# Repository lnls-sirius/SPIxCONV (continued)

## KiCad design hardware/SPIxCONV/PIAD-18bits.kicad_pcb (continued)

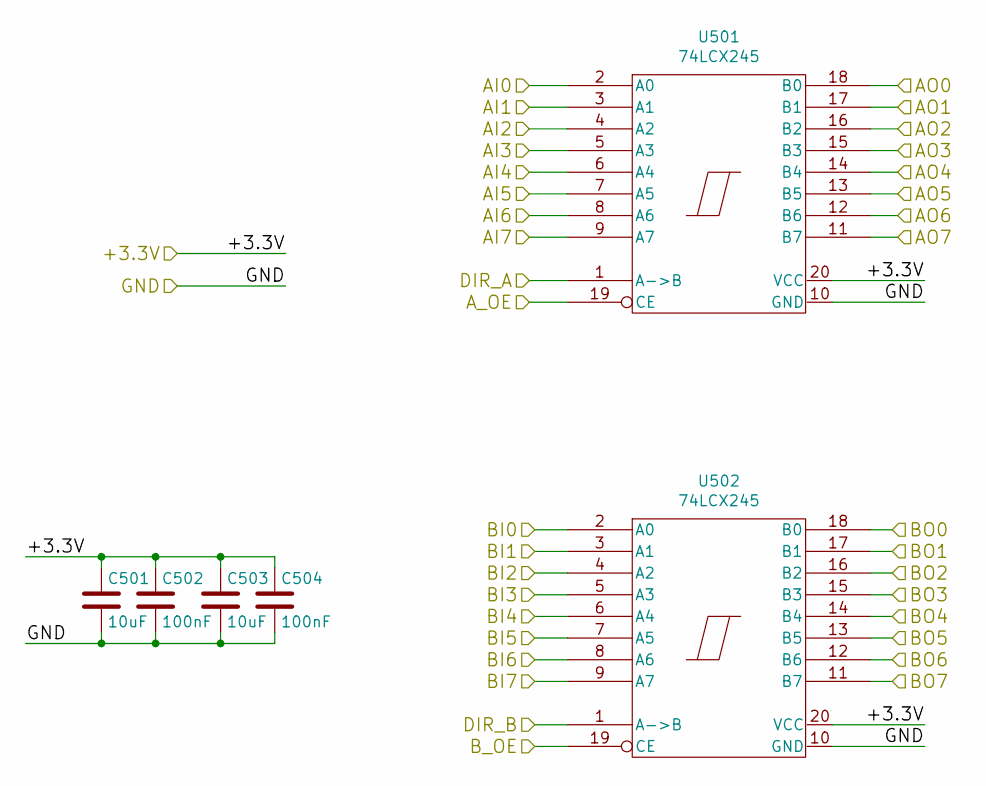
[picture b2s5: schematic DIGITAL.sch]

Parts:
C501, C503: 10uF; C_0805
C502, C504: 100nF; C_0805
U501, U502: 74LCX245; SOIC-20W_7.5x12.8mm_Pitch1.27mm

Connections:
+3V3: C501.1, C502.1, C503.1, C504.1, U501.20 (VCC), U502.20 (VCC); also elsewhere on the board
/DA0: U501.2 (A0); also elsewhere on the board
/DA1: U501.3 (A1); also elsewhere on the board
/DA2: U501.4 (A2); also elsewhere on the board
/DA3: U501.5 (A3); also elsewhere on the board
/DA4: U501.6 (A4); also elsewhere on the board
/DA5: U501.7 (A5); also elsewhere on the board
/DA6: U501.8 (A6); also elsewhere on the board
/DA7: U501.9 (A7); also elsewhere on the board
/DB0: U502.2 (A0); also elsewhere on the board
/DB1: U502.3 (A1); also elsewhere on the board
/DB2: U502.4 (A2); also elsewhere on the board
/DB3: U502.5 (A3); also elsewhere on the board
/DB4: U502.6 (A4); also elsewhere on the board
/DB5: U502.7 (A5); also elsewhere on the board
/DB6: U502.8 (A6); also elsewhere on the board
/DB7: U502.9 (A7); also elsewhere on the board
/DIR_A: U501.1 (A->B); also elsewhere on the board
/DIR_B: U502.1 (A->B); also elsewhere on the board
/PA0: U501.18 (B0); also elsewhere on the board
/PA1: U501.17 (B1); also elsewhere on the board
/PA2: U501.16 (B2); also elsewhere on the board
/PA3: U501.15 (B3); also elsewhere on the board
/PA4: U501.14 (B4); also elsewhere on the board
/PA5: U501.13 (B5); also elsewhere on the board
/PA6: U501.12 (B6); also elsewhere on the board
/PA7: U501.11 (B7); also elsewhere on the board
/PB0: U502.18 (B0); also elsewhere on the board
/PB1: U502.17 (B1); also elsewhere on the board
/PB2: U502.16 (B2); also elsewhere on the board
/PB3: U502.15 (B3); also elsewhere on the board
/PB4: U502.14 (B4); also elsewhere on the board
/PB5: U502.13 (B5); also elsewhere on the board
/PB6: U502.12 (B6); also elsewhere on the board
/PB7: U502.11 (B7); also elsewhere on the board
GND: C501.2, C502.2, C503.2, C504.2, U501.10 (GND), U501.19 (CE), U502.10 (GND), U502.19 (CE); also elsewhere on the board

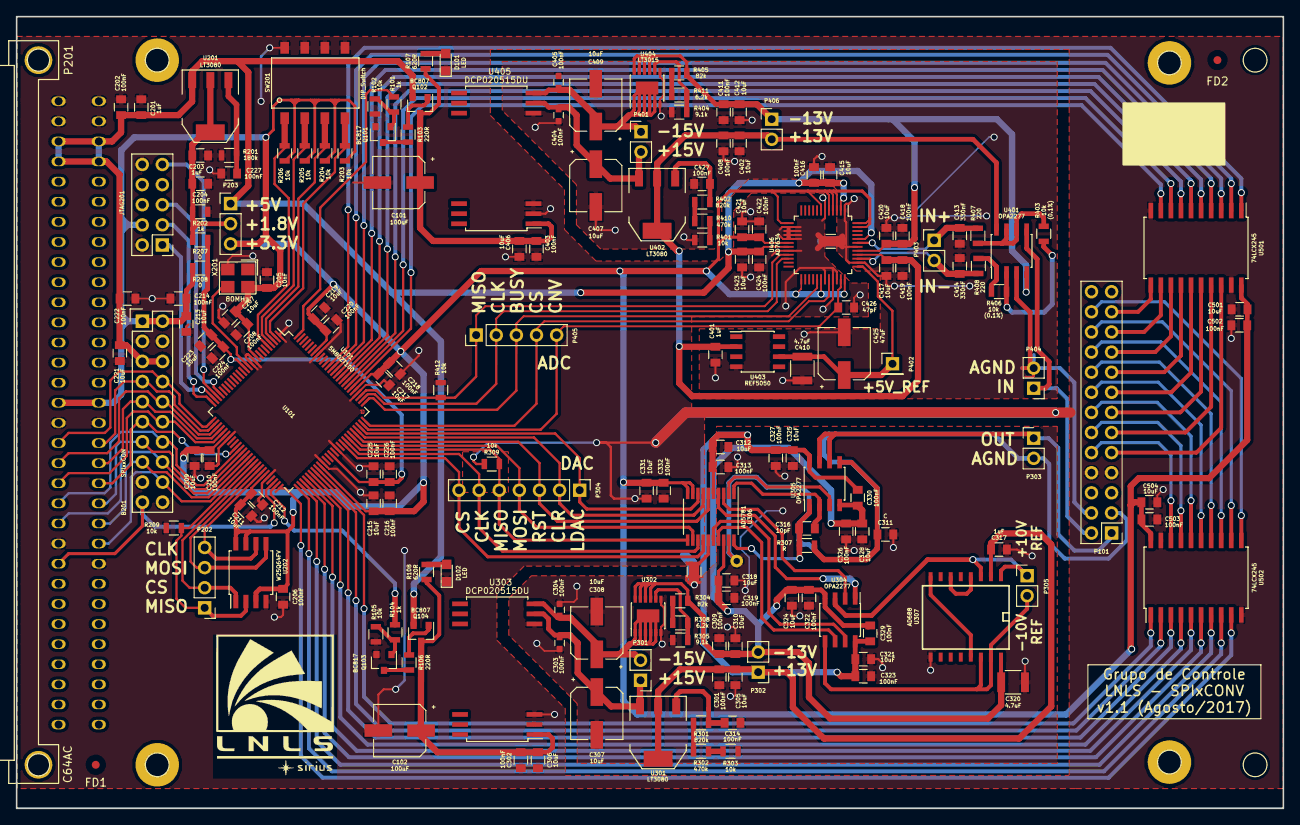
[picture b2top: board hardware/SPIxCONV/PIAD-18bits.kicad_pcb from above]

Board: 2 copper layers, 160.0 x 100.0 mm, 178 parts (0 on the bottom side), 130 nets.

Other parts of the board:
FD1, FD4: Fiducial_1mm_Dia_2.54mm_Outer_CopperBottom
FD2, FD3: Fiducial_1mm_Dia_2.54mm_Outer_CopperTop

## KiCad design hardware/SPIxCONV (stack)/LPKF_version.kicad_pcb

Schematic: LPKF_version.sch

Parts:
Beagle101: BeagleBone; BEAGLEBONEBLACK
P101: CONN_01X05; Pin_Header_Straight_1x05_Pitch2.54mm
P102: CONN_01X07; Pin_Header_Straight_1x07_Pitch2.54mm
P103: CONN_02X02; Pin_Header_Straight_2x02_Pitch2.54mm
P104, P105, P106, P107: CONN_01X01; ground_plane_via
P108: CONN_01X02; Pin_Header_Straight_1x02_Pitch2.54mm
P109: CONN_01X01; Pin_Header_Straight_1x01_Pitch2.54mm
U101, U102: HC245; SOIC-20W_7.5x12.8mm_Pitch1.27mm

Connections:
/+5V: Beagle101.C5, Beagle101.C6, P108.1, P108.2, U101.20, U102.20
/ADC_BUSY: P101.3, U102.7
/ADC_CLK: P101.2, U102.8
/ADC_CNV: P101.5, U102.5
/ADC_CS: P101.4, U102.6
/ADC_MISO: P101.1, U102.9
/DAC_CLK: P102.6, U101.3
/DAC_CLR: P102.2, U101.7
/DAC_CS: P102.7, U101.2
/DAC_LDAC: P102.1, U101.8
/DAC_MISO: P102.5, U101.4
/DAC_MOSI: P102.4, U101.5
/DAC_RST: P102.3, U101.6
/GPIO_BUSY: Beagle101.C16, U102.13
/GPIO_CLR: Beagle101.C25, U101.13
/GPIO_CNV: Beagle101.C14, U102.15
/GPIO_LDAC: Beagle101.C24, U101.12
/GPIO_RST: Beagle101.C26, U101.14
/PWR_SYS: Beagle101.C23, P109.1
/SPI0_CS: Beagle101.C17, U102.14
/SPI0_MISO: Beagle101.C18, U102.11
/SPI0_SCLK: Beagle101.C22, U102.12
/SPI1_CS0: Beagle101.C28, U101.18
/SPI1_MISO: Beagle101.C30, U101.16
/SPI1_MOSI: Beagle101.C29, U101.15
/SPI1_SCLK: Beagle101.C31, U101.17
GND: Beagle101.C1, Beagle101.C2, Beagle101.C43, Beagle101.C44, Beagle101.C45, Beagle101.C46, P103.1, P103.2, P103.3, P103.4, U101.1, U101.10, U101.19, U102.1, U102.10, U102.19

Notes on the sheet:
SPI0: ADC SPI1: DAC

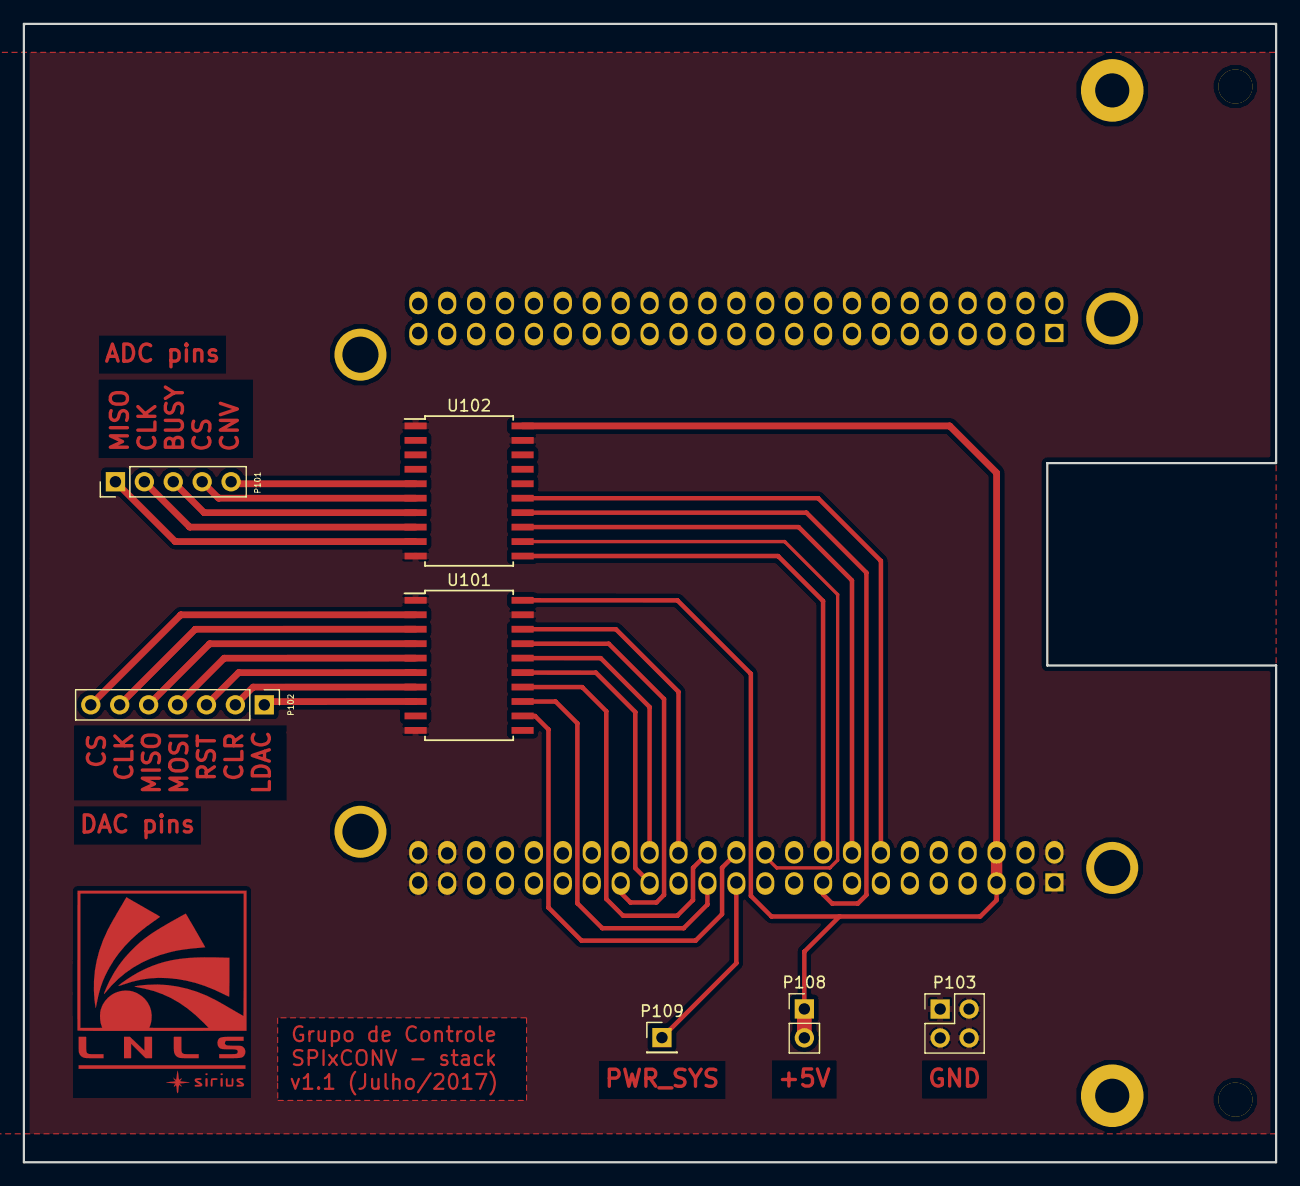
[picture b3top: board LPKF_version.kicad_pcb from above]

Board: 2 copper layers, 110.0 x 100.0 mm, 13 parts (1 on the bottom side), 27 nets.

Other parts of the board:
P102#2: CONN_01X07; LNLS_LOGO_Silk

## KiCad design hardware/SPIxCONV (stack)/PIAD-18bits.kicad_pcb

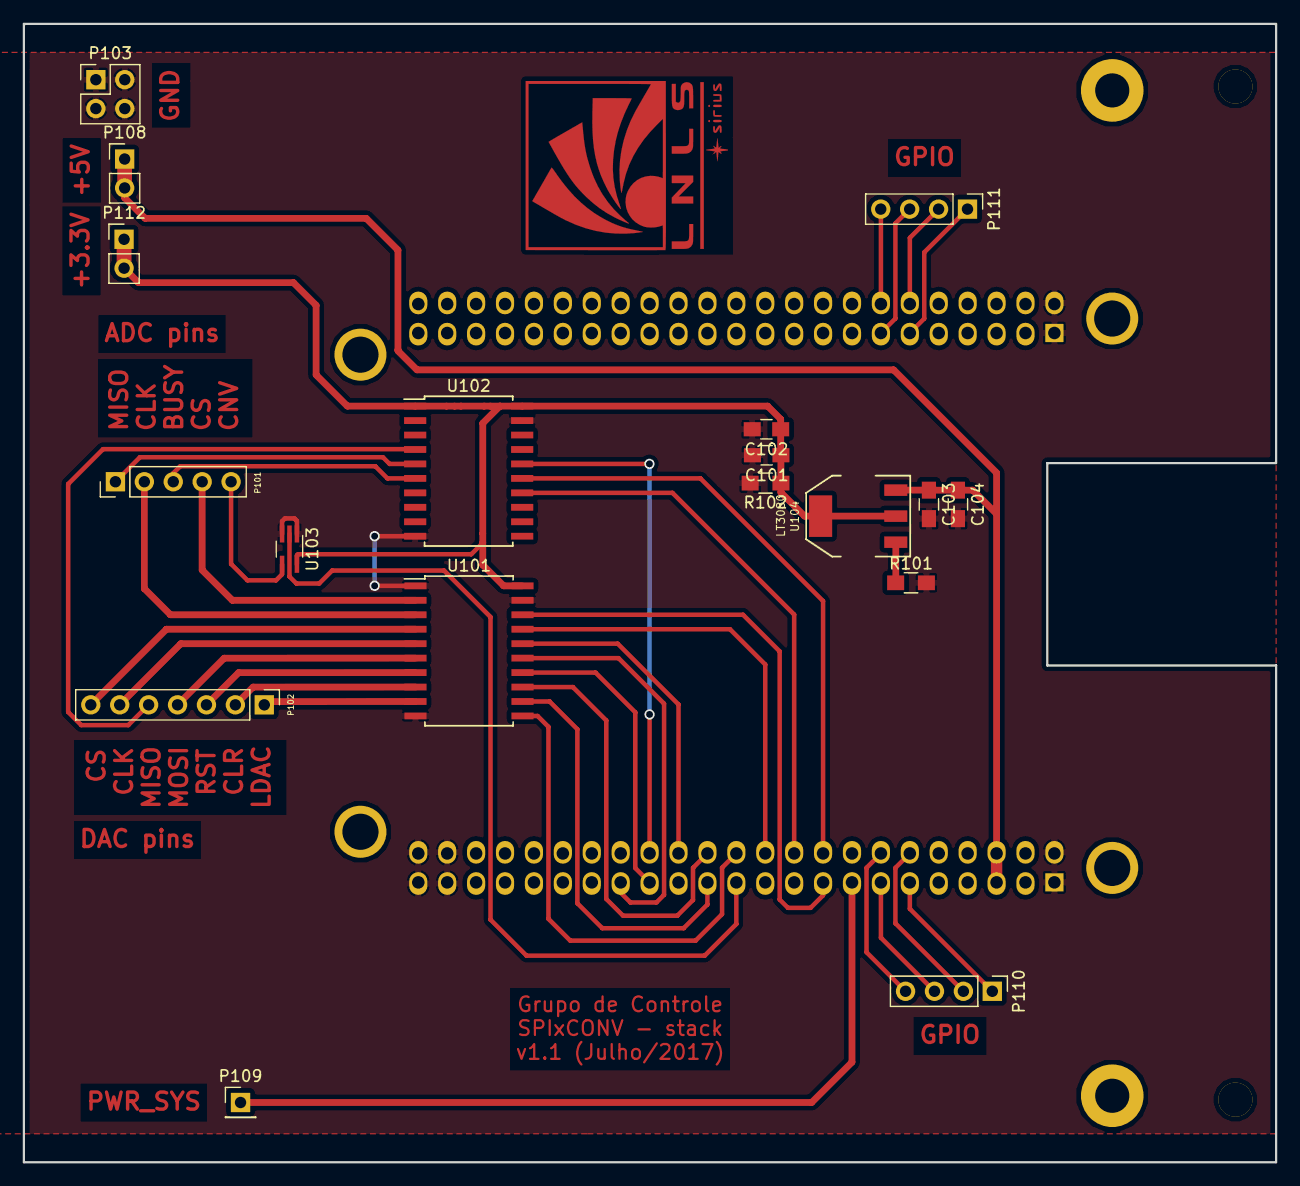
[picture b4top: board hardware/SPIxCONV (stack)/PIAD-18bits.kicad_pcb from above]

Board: 2 copper layers, 110.0 x 100.0 mm, 24 parts (1 on the bottom side), 36 nets.

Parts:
Beagle101: BeagleBone; BEAGLEBONEBLACK
C101, C103: 1uF; C_0805_HandSoldering
C102, C104: 100nF; C_0805_HandSoldering
P101: CONN_01X05; Pin_Header_Straight_1x05_Pitch2.54mm
P102: CONN_01X07; Pin_Header_Straight_1x07_Pitch2.54mm
P102#2: CONN_01X07; LNLS_LOGO_Silk
P103: CONN_02X02; Pin_Header_Straight_2x02_Pitch2.54mm
P104, P105, P106, P107: CONN_01X01; ground_plane_via
P108, P112: CONN_01X02; Pin_Header_Straight_1x02_Pitch2.54mm
P109: CONN_01X01; Pin_Header_Straight_1x01_Pitch2.54mm
P110, P111: CONN_01X04; Pin_Header_Straight_1x04_Pitch2.54mm
R101: 330k; R_0805_HandSoldering
R102: 1k; R_0805_HandSoldering
U101, U102: 74LCX245; SOIC-20W_7.5x12.8mm_Pitch1.27mm
U103: 74LS125; SOT-353_SC-70-5_Handsoldering
U104: LT3080; SOT-223

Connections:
/+3.3V: C101.1, C102.1, P112.1, P112.2, R102.1, U101.20, U102.1, U102.20, U104.2, U104.4
/+5V: Beagle101.C5, Beagle101.C6, C103.1, C104.1, P108.1, P108.2, U104.3
/ADC_BUSY: P101.3, U102.6
/ADC_CLK: P101.2, U101.3
/ADC_CS: P101.4, U101.2
/ADC_MISO: P101.1, U102.5
/DAC_CLK: P102.6, U101.5
/DAC_CLR: P102.2, U101.8
/DAC_CS: P102.7, U101.4
/DAC_LDAC: P102.1, U101.9
/DAC_MISO: P102.5, U102.4
/DAC_MOSI: P102.4, U101.6
/DAC_RST: P102.3, U101.7
/GPIO_0: Beagle101.C11, P110.1
/GPIO_1: Beagle101.C12, P110.2
/GPIO_2: Beagle101.C13, P110.3
/GPIO_3: Beagle101.C14, P110.4
/GPIO_4: Beagle101.B11, P111.1
/GPIO_5: Beagle101.B12, P111.2
/GPIO_6: Beagle101.B13, P111.3
/GPIO_7: Beagle101.B14, P111.4
/GPIO_BUSY: Beagle101.C20, U102.14
/GPIO_CLR: Beagle101.C25, U101.12
/GPIO_CNV: Beagle101.C23, U103.2
/GPIO_LDAC: Beagle101.C24, U101.11
/GPIO_RST: Beagle101.C26, U101.13
/PWR_SYS: Beagle101.C15, P109.1
/SPI0_CS: Beagle101.C17, U101.18
/SPI0_MISO: Beagle101.C18, U102.15
/SPI0_SCLK: Beagle101.C22, U101.17
/SPI1_CS0: Beagle101.C28, U101.16
/SPI1_MISO: Beagle101.C30, U102.16
/SPI1_MOSI: Beagle101.C29, U101.14
/SPI1_SCLK: Beagle101.C31, U101.15
GND: Beagle101.B1, Beagle101.B2, Beagle101.C1, Beagle101.C2, Beagle101.C43, Beagle101.C44, Beagle101.C45, Beagle101.C46, C101.2, C102.2, C103.2, C104.2, P103.1, P103.2, P103.3, P103.4, R101.2, R102.2, U101.1, U101.10, U101.19, U102.10, U102.19, U103.1, U103.3
unnamed: R101.1, U104.1

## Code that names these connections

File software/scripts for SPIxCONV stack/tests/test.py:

#!/usr/bin/python3

from Adafruit_BBIO.SPI import SPI
import Adafruit_BBIO.GPIO as GPIO
import time
#-------------------------------------------------------
# initialize the bus and device /dev/spidev1.0
spi0 = SPI(0,0)     #ADC
# initialize the bus and device /dev/spidev2.0
spi1 = SPI(1,0)     #DAC
#-------------------------------------------------------
#Set the maximum clock frequency
spi0.msh=100000
spi1.msh=100000
#-------------------------------------------------------
# mnemonics for GPIO
RST = "P9_26"
CLR = "P9_25"
LDAC = "P9_24"
BUSY = "P9_20"
CNV = "P9_23"
PWR_SYS = "P9_16"
#PWR_SYS = "P9_15"
#-------------------------------------------------------
# defining outputs
GPIO.setup(RST, GPIO.OUT)
GPIO.setup(CLR, GPIO.OUT)
GPIO.setup(LDAC, GPIO.OUT)
GPIO.setup(CNV, GPIO.OUT)
GPIO.setup(PWR_SYS, GPIO.OUT)
#-------------------------------------------------------
# defining inputs
GPIO.setup(BUSY, GPIO.IN)
#-------------------------------------------------------
# initialization of outputs
GPIO.output(RST, GPIO.LOW)
GPIO.output(CLR, GPIO.LOW)
GPIO.output(LDAC, GPIO.LOW)
GPIO.output(CNV, GPIO.LOW)
GPIO.output(PWR_SYS, GPIO.LOW)
#=======================================================
#	pinout for DAC and ADC bus
#=======================================================
'''
DAC pins
	SPI1_CS:	"P9_28"
	SPI1_SCLK:	"P9_31"
	SPI1_MOSI:	"P9_29"
	SPI1_MISO:	"P9_30"
	GPIO_RST:	"P9_26"
	GPIO_CLR:	"P9_25"
	GPIO_LDAC:	"P9_24"

ADC pins
	SPI0_CS:	"P9_17"
	SPI0_SCLK:	"P9_22"
	SPI0_MISO:	"P9_18"
	GPIO_BUSY:	"P9_20"
	GPIO_CNV:	"P9_23"

GPIO pins
	GPIO_0: "P9_11"
	GPIO_1: "P9_12"
	GPIO_2: "P9_13"
	GPIO_3: "P9_14"

	GPIO_4: "P8_11"
	GPIO_5: "P8_12"
	GPIO_6: "P8_13"
	GPIO_7: "P8_14"

POWER SYSTEM:
	PWR_SYS = "P9_16"
'''
#=======================================================
#	testing SPI
#=======================================================

while(1):
	# RST = 1 --> address
#	GPIO.output(RST, GPIO.HIGH)
#	time.sleep(0.001)
	# RST = 0 --> slaves
#	GPIO.output(RST, GPIO.LOW)
#	time.sleep(0.001)

	# send data through SPI
	spi1.writebytes([0x20, 0x03, 0x12])
	spi0.writebytes([0x02, 0x30, 0x21])

#	GPIO.output(PWR_SYS, GPIO.HIGH)
#	GPIO.output(RST, GPIO.HIGH)
#	GPIO.output(CLR, GPIO.HIGH)
#	GPIO.output(LDAC, GPIO.HIGH)
#	GPIO.output(CNV, GPIO.HIGH)

#	GPIO.output(PWR_SYS, GPIO.LOW)
#	GPIO.output(RST, GPIO.LOW)
#	GPIO.output(CLR, GPIO.LOW)
#	GPIO.output(LDAC, GPIO.LOW)
#	GPIO.output(CNV, GPIO.LOW)

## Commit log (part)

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2016-11-03 Added protection by new line on ConfigByHotname file
2018-12-07 SPIxCONV project cloned from LNLS internal git server
2018-12-07 added "cpld" folder with email for contact
2019-01-14 splitted default window (EPP_SPIxCONV) in Kicker and Septum
2019-01-31 Added support for TCP.
2019-01-31 Removed with resource in order to use Python 2
2019-01-31 Incorrect ident.
2019-01-31 Added logging information to function on(addr)
2019-01-31 Removed comments and fixed bugs when logging server_address
2019-01-31 Fixed a bug in the selection script by adding and %8 operation on the checks.
2019-02-11 Removed logger from DAC.
2019-02-11 Added argparse.ArgumentDefaultsHelpFormatter.
2019-02-19 minor changes
2019-02-19 added "return" value to functions in flash.py
2019-02-28 updated PV name from "PREFIX:PwrState-Mon" to "PREFIX:PwrState-Sts" in CSS displays
2019-03-06 changed executable permission of config-pin
2019-03-06 pinout documentation review
2019-03-06 first PyDM display added
2019-03-06 PyDM ui displays added
2019-05-03 minor changes in displays
2019-05-03 system variables edited in SPIxCONV protocol file
2019-05-07 remaining Pulsed Magnets displays added
2019-05-08 graphs for Voltage-Mon deleted
2019-05-14 ADC measure returning maximum of 10 last samples
2019-05-27 pydm: Added a desktop icon and an install script
2019-06-03 desktop shortcut added
2019-07-27 fixed displays function names
2019-10-07 added multiple devices displays
2019-10-25 changed bit 4 of port B to output (port B: 3 inputs, 5 outputs)
2020-01-06 Support for python3
    Python2 will be deprecated. Changes on "print" commands!
2020-01-28 removed board address ID dependency (requirement: one BBB for each SPIxCONV)
2020-02-04 fixed board address detection bug
2020-02-04 uncommented board_address argument
2020-02-04 discarded board ID (data[0]) information sent by IOC
2020-02-04 bug fixed
2020-02-04 discarded args.board_address information from config
2020-05-15 docs dir added
2020-05-15 [docs] added Sphinx source & build dir
2020-05-15 Â[docs] added github target in Makefile
2020-05-15 [docs] added gh-pages files
2020-05-15 [docs] Makefile updated
2020-05-22 [docs] gh-pages branch initialized
2020-07-13 [voltage-adjustment] queue architecture adopted
2020-07-13 [voltage-adjustment] voltage adjustment commands queue added
2020-07-13 [pulse-sts] pin direction configured
2020-07-13 [voltage-adjustment] fields added to DAC output message (voltage factor, step trigger and delay)
2020-07-14 [voltage-adjustment] fixed fields in DAC output message
2020-07-15 [voltage-adjustment] voltage steps implemented
2020-07-15 [voltage-RB] voltage RB measure at IOC initialization
2020-07-15 [voltage-adjustment] started fix for power PS on with setpoint
2020-07-16 [voltage-adjustment] finished fix for power PS on with setpoint
2020-07-16 [voltage-adjustment] removed print line
2020-07-16 [voltage-adjustment] check last voltage setpoint at code initialization
2020-07-16 [voltage-adjustment] use PwrState-Sel instead of PwrState-Sts for algorithm
2020-07-17 Commented unnecessary protocol code
2020-07-22 [voltage-steps] included hostname support to initialize steps vars
2020-07-22 [voltage-steps] removed rule to adjust setpoint directly if PS is off
2020-07-22 [voltage-steps] last_setpoint fix
2020-07-22 [voltage-steps] last_setpoint initialization
2020-07-22 [voltage-steps] included debug logs for voltage adjustment
2020-07-22 [voltage-steps] changed log level from debug to info
2020-07-22 [voltage-steps] logs added
2020-07-22 [voltage-steps] logs related to hostname added
2020-07-22 [voltage-steps] ensure RB is equal to RB
2020-07-22 [voltage-steps] send SP to RB
2020-07-27 [voltage-steps] added try/except for threads 2 and 3
2020-07-27 [voltage-steps] changed identifier from hostname to ip address
2020-07-27 [voltage-steps] included steps var in identifier
2020-07-27 [voltage-steps] started using terminator for messages (CR+LF)
2020-07-29 [voltage-adjustment] removed print and added terminator characters (CR+LF)
2020-07-29 [voltage-adjustment] lock support to avoid race conditions included
2020-07-30 [voltage-adjustment] changed logs setpoint unit (from code to voltage)
2020-07-30 [voltage-adjustment] included step number in logs (for gradual adjustments)
2020-07-30 [voltage-adjustment] restored rule to stop gradual adjustments if a new setpoint is received
2020-07-30 [voltage-adjustment] PS on/off & Pulse on/off logs included
2020-07-30 [voltage-adjustment] added logs to write commands
2020-07-31 [voltage-adjustment] changed line split method (break only CR+LF)
2020-07-31 [voltage-adjustment] changed command 0x0D to 0x11
2020-08-14 hostname support for spares
2020-08-17 general spare support added
2020-09-15 [readme] simple description added
2020-09-15 hardware figures dir created
2020-09-15 [readme] cut figures and added them to readme
2020-09-15 [readme] pcb figs and link to github-page added
2020-09-16 connectors figure added
2020-09-16 [readme] connectors image added
2020-09-16 [readme] GPIO expander board info added
2020-09-16 [readme] main board and gpio stack added
2020-09-17 [readme] main board image added
2020-09-17 [readme] software files location added
2020-09-17 [readme] code, known problems, faq sections added under software section
2020-09-17 [readme] software description added
2020-09-17 [readme] OPI section added
2020-09-17 Update README.md: Fix broken image link
2020-09-17 [readme] OPI image added
2020-09-17 [readme] updated images
2020-09-17 [readme] side-by-side images
2020-09-17 [readme] fixed broken links
2020-09-17 [readme] images config updated
2020-09-17 [readme] images updated
2020-09-17 [readme] CPLD pinout added
2020-09-18 figure rotated (main board)
2020-09-18 gpio images rotated
2020-09-18 main board figures rotated
2020-09-18 figures path updated
2020-09-21 [readme] figures updated
2020-09-21 [readme] main board division figures added
2020-09-21 [readme] main board: testpoints figures added
2020-09-21 [readme] gpio stack: testpoints figures added
2020-09-21 [readme] main board division updated
2020-09-23 [documentation] fixed dac & adc selections
2020-09-23 [documentation] fixed typo in CPLD connector figure
2020-09-23 [documentation] figures of interface connectors in GPIO stack updated
2020-09-23 [readme] add calibration figures
2020-09-23 [readme] add CPLD figures
2020-09-23 [readme] main board testpoint section created
2020-09-23 [readme] gpio test point section created
2020-09-23 [documentation] changed figures extension (png --> jpg)
2020-09-23 [documentation] images compressed (jpeg)
2020-09-23 [readme] images extension updated (jpeg)
2020-09-23 [documentation] figures updated (rotated, cut, divison redone)
2020-09-23 [readme] voltmeter datasheet added and calibration section updated
2020-09-23 [readme] add calibration data
2020-09-23 [readme] fixed calibration data table
2020-09-23 [readme] add known problems
2020-11-12 correction from last commit
2020-11-12 loop while-pass removed
2021-02-23 Adding config with hostname info
2021-03-19 Added analog feedback project
2021-05-05 Added configuration to set the BBB hostname via an external flash drive
2021-05-06 Removed pycache
2021-05-06 Added umont /dev/sda command
2021-09-30 Redis script for Voltage Feedback
2021-09-30 Script update
2023-02-06 upgrading code for new nlk
2023-02-06 removing unused files
2023-02-06 config at ioc startup
2023-02-08 Updates for reading 3 boards
2023-02-08 Minor update
2023-02-14 removing prints
2023-09-05 Removing print from dacpy, reducing SPI BR and config NLK hostname
2023-10-16 Update spixconv_unix_socket.py
    New crate names !
2023-11-07 Identation bug
2023-11-13 Update spixconv_unix_socket.py
    Add a `time.sleep` for waiting for next setpoint instead of checking if queue is not empty (mandatory for use with more than one board)
2024-03-06 spixconv_socket.py: add keepalive option for socket connection
    Prevents unknown broken connections
2024-09-05 spixconv_socket.py: remove print
2024-09-05 spixconv_socket.py: Add rotating file logging handler
2024-09-24 spixconv_unix_socket.py: restore removed line for argparse
2025-07-01 Add structured response format to socket protocol
    Updated the communication protocol to include explicit command
    tracking in responses. Each reply now follows the format:
    `[command][status][data][checksum]\r\n`,
    where `status` is currently hardcoded to `0x01` (success). Checksum
    covers the full payload (command + status + data). Error handling
    will be added in a future update.
2025-07-08 Change loop definition
    This updates the loop definition to match an unmerged modification
    introduced in the logging branch. This ensures consistency between
    the two branches.
2025-07-08 Add structured response format to socket protocol (no checksum)
    Updated the communication protocol to include explicit command
    tracking in responses. Each reply now follows the format:
    `[command][status][data]\r\n`
    The status byte is currently hardcoded to 0x01 (success).
    The checksum field, previously part of the response format,
    was removed in a prior commit and will be reintroduced in a future
2025-08-18 Clean up old comments in `spixconv_unix_socket.py`
2025-08-18 Refactor functions out of `if __name__ == '__main__'` block
    Move `voltage_steps`, `voltage_adjustment`, `read_from_list` and
    `write_to_list` outside the main block. Made `queue_general`,
    `queue_voltage` and `args` global for accessibility.
2025-08-20 Update IOC protocol file
    Add the current version of the .proto file being used in the IOC.
    This updated protocol file matches the more informative header
    (`[command][status][data]\r\n`) discussed in previous commits.
    Also, this new header provides a mismatch handler that is
    responsible for detecting and handling out-of-sync messages,
    ensuring proper synchronization between the IOC and BeagleBone.
2025-08-20 Remove debug messages flooding the log
2025-08-20 Change queue module name
    - In Python2 it was `from Queue import Queue`
    - In Python3 it is `from queue import queue`
2025-08-21 Change shebang
2025-08-21 Fix `print` syntax
2025-08-22 Handle bytes/strings correctly in `spixconv_unix_socket.py`
    Update socket handling in `spixconv_unix_socket.py` for Python 3
    compatibility. All received data is now treated as `bytes`, with
    proper decoding when converting to integers and encoding when
    sending responses. Replaces `ord()` and `int()` on `str` with
    appropriate `bytes` handling.
2025-08-22 Correct bytes/strings handling in `flash.py`
2025-08-22 Refactor `script_read` and `script_write`
2025-08-22 Further bytes/strings adjustments in `spixconv_unix_socket.py`
    Additional fixes to Python 3 compatibility, ensuring all socket
    data is handled consistently and decoding/encoding is robust.
2025-08-22 Fix Python 3 compatibility in `sector_write`
    replace `/` with `//` to ensure integer division for list indexing
2025-10-31 Remove full command log
2025-11-06 Ensure correct integer conversion in `queue_general.put()`
    Replaced `.decode("ascii")` on single-byte values with `bytes([...])`
    to ensure correct integer conversion in `queue_general.put()`.
2025-11-06 Fix command parsing for `set_direction_bit`
    Decode port, bit, and value correctly.
2025-11-06 Fix command 0x07 log entry
2025-12-12 Add changelog and version files for v0.1.0 initial public release
2025-12-12 Document Updated Bit Usage: Pulse-Sts and New Interlock 9 Assignment
    This commit updates the documentation files, specifically the .ods spreadsheet and the
    rendered .jpeg figure, to reflect two changes in bit usage within the IOC B-A connector
    interface. First, it documents that bit B4 (pin 18) is used for reading the Trigger
    Pulse status (Pulse-Sts) from the source. Second, it records the assignment of
    Interlock 9 to bit B5 (pin 20), which was previously unused.
